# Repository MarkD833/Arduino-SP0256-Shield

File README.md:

# Arduino UNO General Instruments SP0256-AL2 Shield
After playing with the National Semiconductor Digitalker IC, I got to remembering about another speech chip from my younger days. Way back when I owned a [NASCOM-2](https://en.wikipedia.org/wiki/Nascom) Z80 based machine, I also had a speech interface built around a GI SP0256-AL2 device that I hooked up to it. This is my spin on using the SP0256-AL2 chip with a modern-ish Arduino UNO board.

## Description

The aim of this project is to create a shield for an Arduino UNO to bring to life a General Instruments SP0256-AL2 speech IC and to additionall have some non-volatile storage to hold some [allophones](https://en.wikipedia.org/wiki/Allophone) for pre-defined words and phrases.

## Design

In order to speak a word (or phrase), the SP0256-AL2 needs to be passes a stream of allophones that when strung together sound like a word. The SP0256-AL2 has 64 allophones. The required allophone is presented on the pins A1..A8. In this design, A7 & A8 are grounded so only 6 bits are used from the shift register.

Once the required allophone has been presented, the ALD (Address Load) pin is pulsed low briefly. This loads the allophone into the SP0256-AL2 and starts the sound generation process.

The SP0256-AL2 sets the LRQ (Load Request) pin low when it is ready for the next allophone.

### Interface

I've chosen to use the SPI interface of the ATMEGA328P on the UNO and a single 74HCT595 serial-in / parallel-out shift register to transfer the allophone to the SP0256-AL2 chip.

I'm using the SPI signals MOSI and SCK from the ICSP header on the UNO rather than D11 and D13 in the hope that this board can also be used with an Arduino MEGA2560 as well. The SPI signals on the Arduino MEGA2560 board are on completely different pins, but they are also present on the ICSP header in the same physical location as on the UNO.

The SPI SS signal is routed to the D10 pin on the UNO, the Address Load is routed to the A1 pin on the UNO and the Load Request is routed to pin A0 on the UNO.

### Power

Unlike the Digitalker chip, the SP0256-AL2 runs from 5V which is sourced from the UNO board. 

### Audio

The audio circuitry is lifted directly from the SP0256-AL2 datasheet.

# The Arduino UNO Shield

An assembled shield (missing the EEPROM chip).

# Assembly

Start with the discrete components - there are a few resistors and capacitors which should be easy to hand solder. Then add the various IC sockets and the header pins.

The header pins are best inserted into the Arduino UNO board first and then the shield placed on to of them. That way all the headers will be vertical and mate up with the UNO sockets properly.

When you've installed all the basic components, and before fitting any chips, check that you have 5V on the VCC pins of the SP0256-AL2, 74HCT595 and 25LC256.

Install the SP0256-AL2, 74HCT595 and the 25LC256 EEPROM. 

# Speaking the first words

I've created a simple test sketch that you can use to send any of the allophones. It's in the code folder and called ALLOTEST. You can type in either the allophone number (0-63) or the allophone name. Multiple allophones can be generated - simply put a space between each allophone.
 As a start, the allophones for the word "hello" are:
 
> PA2 HH1 EH LL OW PA1

or

> 1 27 7 45 53 0

Note that the SP0256-AL2 needs a silence allophone such as PA1 at the end of a sequence otherwise it continues to output the last sound it made.

# Bored with trying to work out the required allophones yet?

I discovered a [software implementation of the CTS256 chip](https://github.com/GmEsoft/SP0256_CTS256A-AL2). The CTS256 chip is used to convertt plain ASCII character words into the required allophones that the SP0256-AL2 uses. The software can be compiled using the free version of Visual Studio. Once compiled, you can use the CTS256 simulator to produce the required allophones like this:

> CTS256A-AL2.exe hello
>
> CTS256A-AL2(tm) Emulator - v0.0.6-alpha
>
> PA2 HH1 EH LL OW PA3
>
> Conversion complete.

It's not perfect but it does provide a reasonable starting point for creating your own words.

# On-board vocabulary

The board also includes a 25LC256 EEPROM to store pre-defined sequences of allophones that can be read back and transferred to the SP0256-AL2 chip.

## Creating a library of words

It took a little bit of lateral thinking but I discovered that I could use the free online assembler at [ASM80.com](https://asm80.com) to create Intel Hex records.

I've included a sample library of quite a few words in the code folder called vocab_v1.0.asm. The words are mostly the pre-defined words that are available with the National Semiconductor Digitalker Voice Selection Software (DVSS) and were created using a batch file and a slightly modified version of the CTS256A-AL2 program (see above), followed by some search and replace incantations in NotePad++.

This plain text file can be pasted into a new file on asm80.com (I used the 8080 CPU type when creating the new file).

The layout of the EEPROM memory is detailed in the vocabulary file. Simply, there's a list of 16-bit pointers at the start of memory that point to each sequence of allophones required to sound out a particualr word (or phrase). I simply grouped the words so that all words starting with A are together and all words starting with B are together etc.

Address 0000 holds a 16-bit pointer to a null terminated string that you can use to identify your vocabulary.

Starting at address 0002 are the 16-bit pointers to all the words that begin with A. Starting at address 500 (that's 500 decimal) are the 16-bit pointers to all the words that begin with B. Starting at address 1000 are the 16-bit pointers to all the words that begin with C and so on.

That gives 500 bytes (or 250 16-bit pointers => 250 words) to store all the words beginning with a certain letter. With 26 letters in the alphabet and 250 words per letter, that gives a possible maximum of 6500 words.

If you want to add a new word, then simply tag it on to the end of the group of words with the same first letter. That way you don't need to adjust the number associated with any existing word. Well, not unless you end up with more than 250 words with the same first letter! 

The file is then saved and compiled to produce the Intel-Hex file.

## Programming the vocabulary into the EEPROM

I've created a simple test sketch that you can use to program the on-board EEPROM. Or you can use an external programmer to program the chip. The sketch is in the code folder and called EE_PROG.

With the sketch running, you can then upload the vocabulary using a terminal program such as TeraTerm. I used CoolTerm as it will display the output from the sketch as the upload progresses.

*NOTE:* I had to edit the Intel-Hex file generated by ASM80 to insert a final new line so that the end of file record was processed by the EEPROM programming sketch.

## Accesing the EEPROM vocabulary

I've created a simple sketch to recall the words in the vocabulary. The sketch is in the code folder and called EE_TEST.

To speak one of the stored phrases, just type in the phrase index number. To say the word OK, the index number is 3506 in the vocab v1.0 file.

There's very little error checking in the demonstration code so watch out!

Note that I did hope to check to see if the 16-bit pointer was valid before attempting to retrieve the specific allophone sequence. However, being mindful of the number of write cycles of the EEPROM, I couldn't see a way to return all locations back to $FF before programming a new vocabulary without literally writing $FF to every location manually.

I think that there may be some cleverness within the ASM80 directives that I could use to fill the unused sections of the pointer table with $FF. If I find it, I will update the vocab source file and ammend the demo accordingly. As it stands, any memory location of EEPROM that doesn't get written to when loading the new Intel-Hex file will retain whatever value was in there previously.

# Further information

Have a look in the datasheets folder for information on the SP0256-AL2 chip and its companion, the CTS256. The SP0256-AL2 datasheet details the allophones as well as examples of their use in english words.

# Known errors

* The addition of a 10K pull up resistor on the ALD line stops spurious sounds whilst uploading sketches.

* There may be an issue with the code that handles the writing of the Intel-HEX data to the EEPROM. When trying to load the vocabulary Intel-Hex file using the EE_PROG sketch, the data sometimes got messed up such that only partial words were spoken. I've not figured out whether this is a problem with my code or the EEPROM library as the Intel-Hex file is correct.
 
# Releases

* 0.2
    * New demonstrations sketches
    * New large vocabulary file for the EEPROM
* 0.1
    * Initial Release

## License

This project is licensed under the GNU General Public License v3.0 - see the LICENSE.md file for details

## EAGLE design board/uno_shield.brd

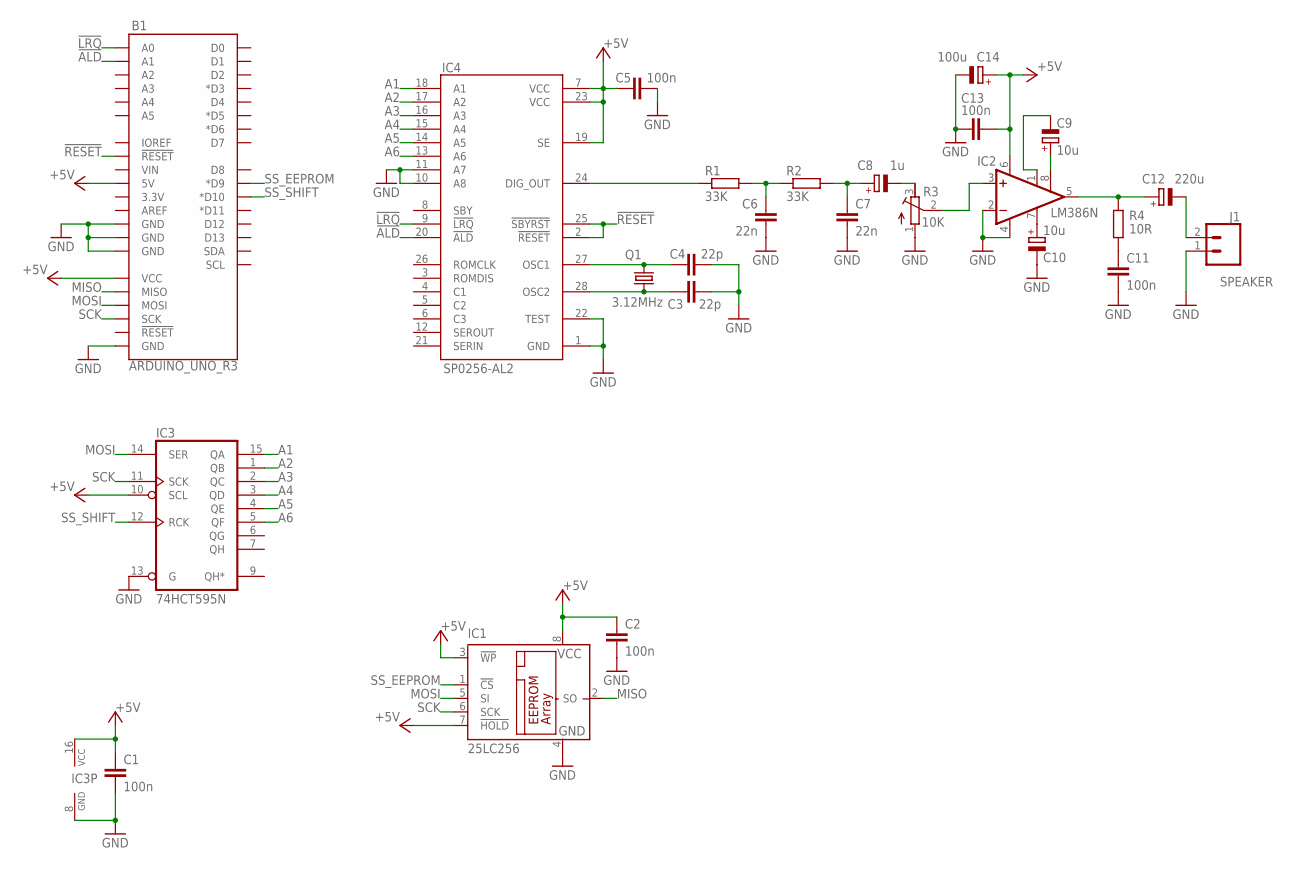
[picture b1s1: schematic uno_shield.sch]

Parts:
B1: ARDUINO_UNO_R3; ARDUINO_R3
C1, C2, C5, C11, C13: 100n; C025-024X044
C3, C4: 22p; C025-024X044
C6, C7: 22n; C025-024X044
C8: 1u; E2,5-7
C9, C10: 10u; E2,5-5
C12: 220u; E2,5-7
C14: 100u; E2,5-7
IC1: 25LC256; DIL8
IC2: LM386N; DIL08
IC3: 74HCT595N; DIL16
IC4: SP0256-AL2; DIL28-6-OCT_PADS
J1: CONN_025MM; SCREWTERMINAL-5MM-2
Q1: 3.12MHz; HC49/S
R1, R2: 33K; 0309/10
R3: 10K; RTRIM3296W
R4: 10R; 0309/10

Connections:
!ALD: B1.A1, IC4.20 (!ALD)
!LRQ: B1.A0, IC4.9 (!LRQ)
!RESET: B1.RESET@1 (!RESET!), IC4.2 (!RESET), IC4.25 (!SBYRST)
+5V: B1.5V, B1.VCC, C1.1, C2.1, C5.1, C13.2, C14.+, IC1.3 (!WP), IC1.7 (!HOLD), IC1.8 (VCC), IC2.6 (VS), IC3.10 (SCL), IC3.16 (VCC), IC4.7 (VCC), IC4.19 (SE), IC4.23 (VCC)
A1: IC3.15 (QA), IC4.18 (A1)
A2: IC3.1 (QB), IC4.17 (A2)
A3: IC3.2 (QC), IC4.16 (A3)
A4: IC3.3 (QD), IC4.15 (A4)
A5: IC3.4 (QE), IC4.14 (A5)
A6: IC3.5 (QF), IC4.13 (A6)
GND: B1.GND@1 (GND), B1.GND@2 (GND), B1.GND@3 (GND), B1.GND@4 (GND), C1.2, C2.2, C3.2, C4.2, C5.2, C6.2, C7.2, C10.-, C11.2, C13.1, C14.-, IC1.4 (GND), IC2.2 (-IN), IC2.4 (GND), IC3.8 (GND), IC3.13 (G), IC4.1 (GND), IC4.10 (A8), IC4.11 (A7), IC4.22 (TEST), J1.1, R3.1 (A)
MISO: B1.MISO, IC1.2 (SO)
MOSI: B1.MOSI, IC1.5 (SI), IC3.14 (SER)
unnamed: IC4.24 (DIG_OUT), R1.1
unnamed: C3.1, IC4.28 (OSC2), Q1.1
unnamed: C4.1, IC4.27 (OSC1), Q1.2
unnamed: C6.1, R1.2, R2.1
unnamed: C7.1, C8.+, R2.2
unnamed: C8.-, R3.3 (E)
unnamed: C9.-, IC2.1 (GAIN)
unnamed: C9.+, IC2.8 (GAIN)
unnamed: C10.+, IC2.7 (BYPASS)
unnamed: C11.1, R4.1
unnamed: C12.+, IC2.5 (OUT), R4.2
unnamed: C12.-, J1.2
unnamed: IC2.3 (+IN), R3.2 (S)
SCK: B1.SCK, IC1.6 (SCK), IC3.11 (SCK)
SS_EEPROM: B1.D9 (*D9), IC1.1 (!CS)
SS_SHIFT: B1.D10 (*D10), IC3.12 (RCK)

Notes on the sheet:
SPEAKER

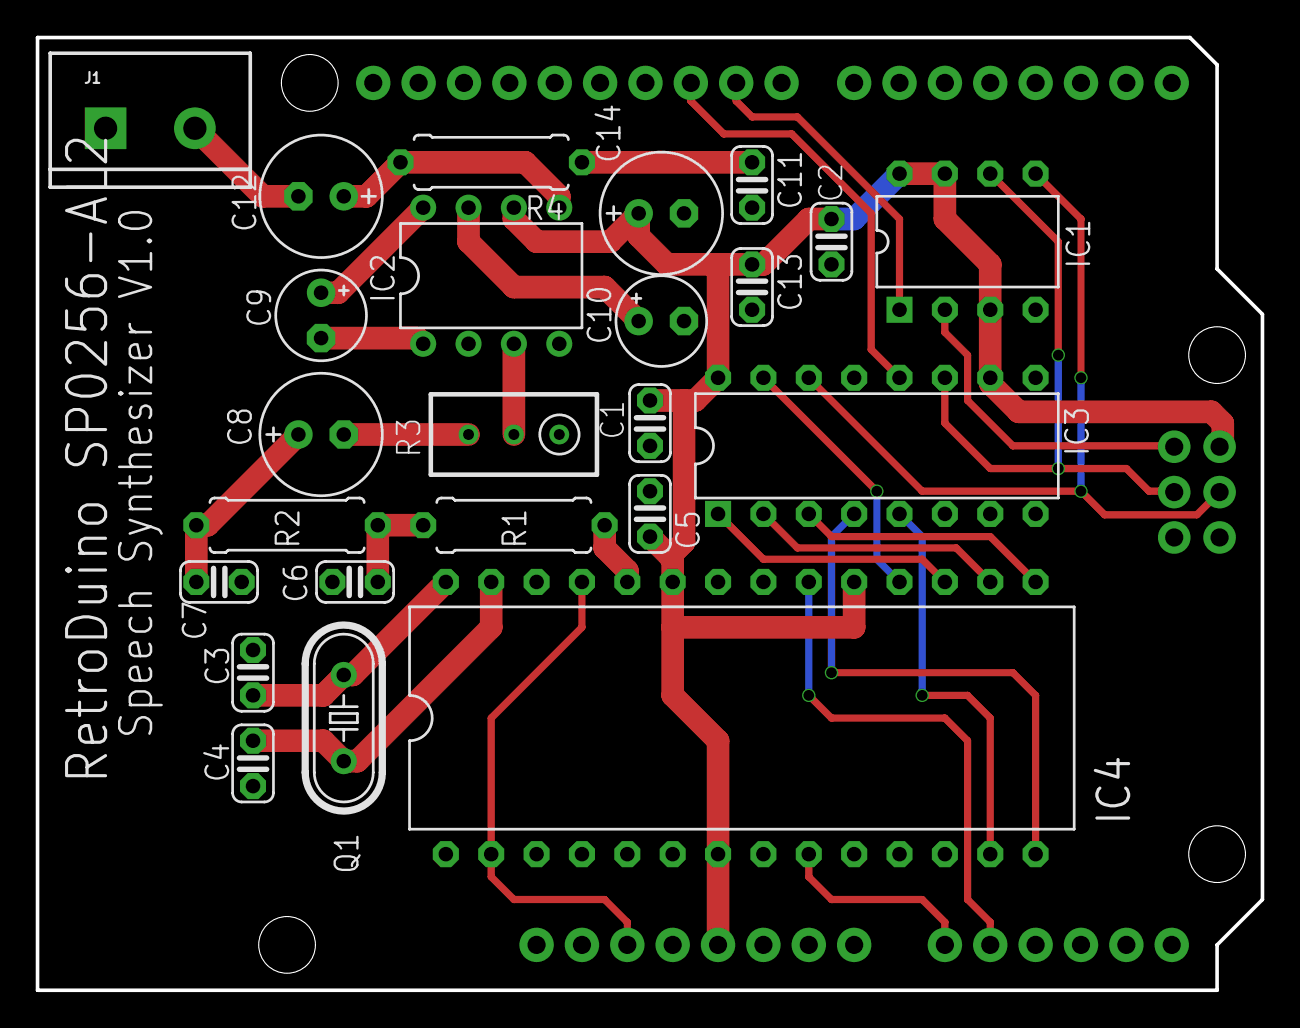
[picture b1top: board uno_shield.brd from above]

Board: 2 copper layers, 68.6 x 53.3 mm, 25 parts (0 on the bottom side), 29 nets.

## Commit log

2024-02-16 correction to readme
2024-02-18 added sample vocabulary
2024-02-18 Added images
2024-02-18 wrong file extensions!
2024-02-18 added note re Arduino EEPROM library
2024-02-27 Added new vocabulary
2024-02-29 New test program & vocabulary
    New test sketch and a 500+ word vocabulary have been added.
2024-03-02 New demo sketches
    Replaced the demo sketches and updated the large vocabulary.
2024-03-03 corrected cut and paste frenzy!
2024-03-03 Hmm subscript doesn't work...
2024-04-17 Updated vocabulary
    Hopefully fixed a bunch of poor sounding words and added a few more new words.

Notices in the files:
parts and their libraries:
SparkFun-Connectors: Licensing: Creative Commons ShareAlike 4.0 International - https://creativecommons.org/licenses/by-sa/4.0
